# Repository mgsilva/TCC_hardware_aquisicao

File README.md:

# TCC - Hardware Aquisição
Layout da PCB do sistema de aquisição utilizado no Trabalho de Conclusão de Curso do CEFET-MG.

Tema: Projeto e implementação de uma plataforma IoT para monitoramento de motores de indução trifásicos.

Este hardware conta com um sensor de corrente, um filtro antialiasing, um conversor de nível e um ESP32.
O sistema é capaz de aquisitar sinais até 5Khz.

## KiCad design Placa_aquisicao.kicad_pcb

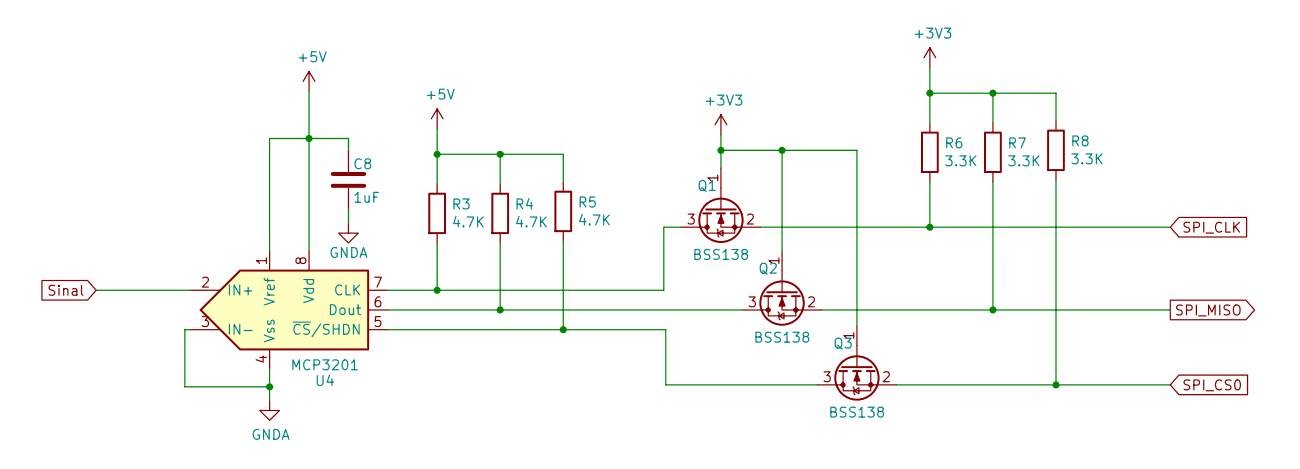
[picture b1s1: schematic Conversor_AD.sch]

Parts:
C8: 1uF; C_0805_2012Metric_Pad1.18x1.45mm_HandSolder
Q1, Q2, Q3: BSS138; SOT-23
R3, R4, R5: 4.7K; R_0805_2012Metric_Pad1.20x1.40mm_HandSolder
R6, R7, R8: 3.3K; R_0805_2012Metric_Pad1.20x1.40mm_HandSolder
U4: MCP3201; SOIC-8_3.9x4.9mm_P1.27mm

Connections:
+3V3: Q1.1 (G), Q2.1 (G), Q3.1 (G), R6.1, R7.1, R8.1; also elsewhere on the board
+5V: C8.1, R3.1, R4.1, R5.1, U4.1 (Vref), U4.8 (Vdd); also elsewhere on the board
GND: C8.2, U4.3 (IN-), U4.4 (Vss); also elsewhere on the board
unnamed: Q1.3 (D), R3.2, U4.7 (CLK)
unnamed: Q2.3 (D), R4.2, U4.6 (Dout)
unnamed: Q3.3 (D), R5.2, U4.5 (~CS~/SHDN)
SPI_CLK: Q1.2 (S), R6.2; also elsewhere on the board
SPI_CS0: Q3.2 (S), R8.2; also elsewhere on the board
SPI_MISO: Q2.2 (S), R7.2; also elsewhere on the board
Sinal: U4.2 (IN+); also elsewhere on the board

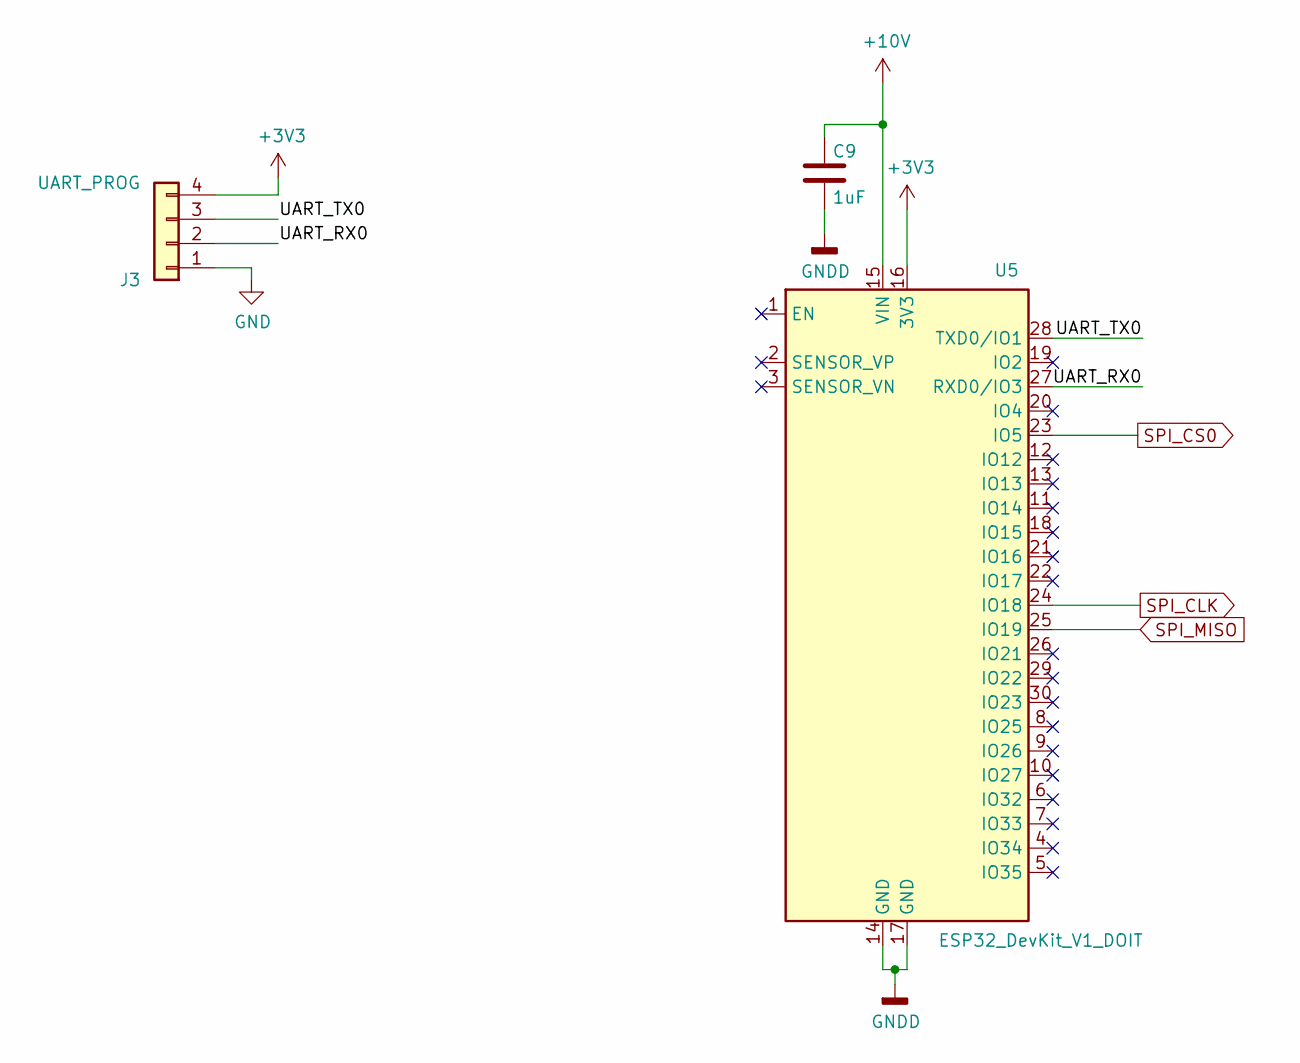
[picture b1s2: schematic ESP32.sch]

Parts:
C9: 1uF; C_0805_2012Metric_Pad1.18x1.45mm_HandSolder
J3: UART_PROG; Molex_KK-254_AE-6410-04A_1x04_P2.54mm_Vertical
U5: ESP32_DevKit_V1_DOIT; esp32_devkit_v1_doit

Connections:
+3V3: J3.4, U5.16 (3V3); also elsewhere on the board
+10V: C9.1, U5.15 (VIN); also elsewhere on the board
/ESP32/UART_RX0: J3.2, U5.27 (RXD0/IO3)
/ESP32/UART_TX0: J3.3, U5.28 (TXD0/IO1)
GND: C9.2, J3.1, U5.14 (GND), U5.17 (GND); also elsewhere on the board
SPI_CLK: U5.24 (IO18); also elsewhere on the board
SPI_CS0: U5.23 (IO5); also elsewhere on the board
SPI_MISO: U5.25 (IO19); also elsewhere on the board

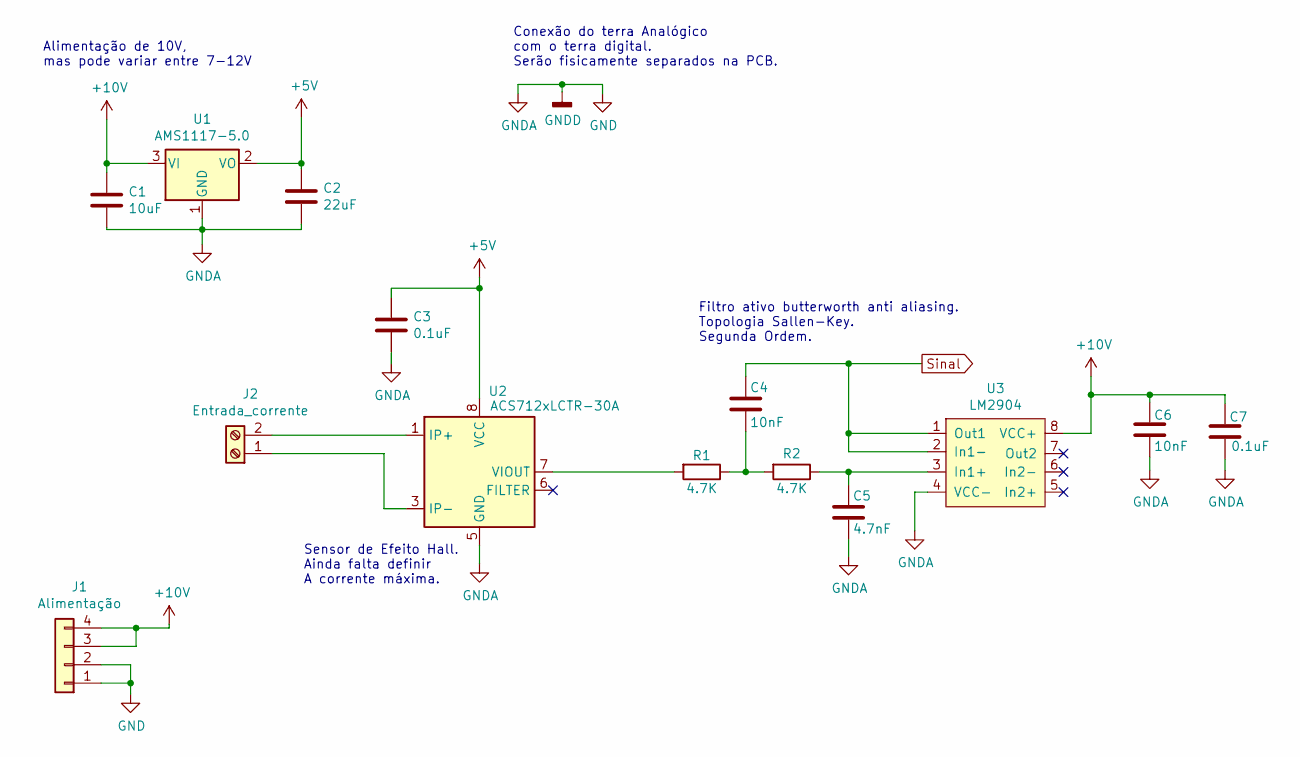
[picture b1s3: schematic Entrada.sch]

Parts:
C1: 10uF; C_0805_2012Metric_Pad1.18x1.45mm_HandSolder
C2: 22uF; C_1206_3216Metric_Pad1.33x1.80mm_HandSolder
C3, C7: 0.1uF; C_0805_2012Metric_Pad1.18x1.45mm_HandSolder
C4, C6: 10nF; C_0805_2012Metric_Pad1.18x1.45mm_HandSolder
C5: 4.7nF; C_0805_2012Metric_Pad1.18x1.45mm_HandSolder
J1: Alimentação; Molex_KK-254_AE-6410-04A_1x04_P2.54mm_Vertical
J2: Entrada_corrente; TerminalBlock_Phoenix_MKDS-1,5-2_1x02_P5.00mm_Horizontal
R1, R2: 4.7K; R_0805_2012Metric_Pad1.20x1.40mm_HandSolder
U1: AMS1117-5.0; SOT-223-3_TabPin2
U2: ACS712xLCTR-30A; SOIC-8_3.9x4.9mm_P1.27mm
U3: LM2904; SO-8_3.9x4.9mm_P1.27mm

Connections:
+5V: C2.1, C3.1, U1.2 (VO), U2.8 (VCC); also elsewhere on the board
+10V: C1.1, C6.1, C7.1, J1.3, J1.4, U1.3 (VI), U3.8 (VCC+); also elsewhere on the board
GND: C1.2, C2.2, C3.2, C5.2, C6.2, C7.2, J1.1, J1.2, U1.1 (GND), U2.5 (GND), U3.4 (VCC-); also elsewhere on the board
unnamed: C4.2, R1.1, R2.2
unnamed: C5.1, R2.1, U3.3 (In1+)
unnamed: J2.1, U2.3 (IP-), U2.4 (IP-)
unnamed: J2.2, U2.1 (IP+), U2.2 (IP+)
unnamed: R1.2, U2.7 (VIOUT)
Sinal: C4.1, U3.1 (Out1), U3.2 (In1-); also elsewhere on the board

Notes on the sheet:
Conexão do terra Analógico com o terra digital. Serão fisicamente separados na PCB.
Filtro ativo butterworth anti aliasing. Topologia Sallen-Key. Segunda Ordem.
Alimentação de 10V, mas pode variar entre 7-12V
Sensor de Efeito Hall. Ainda falta definir A corrente máxima.

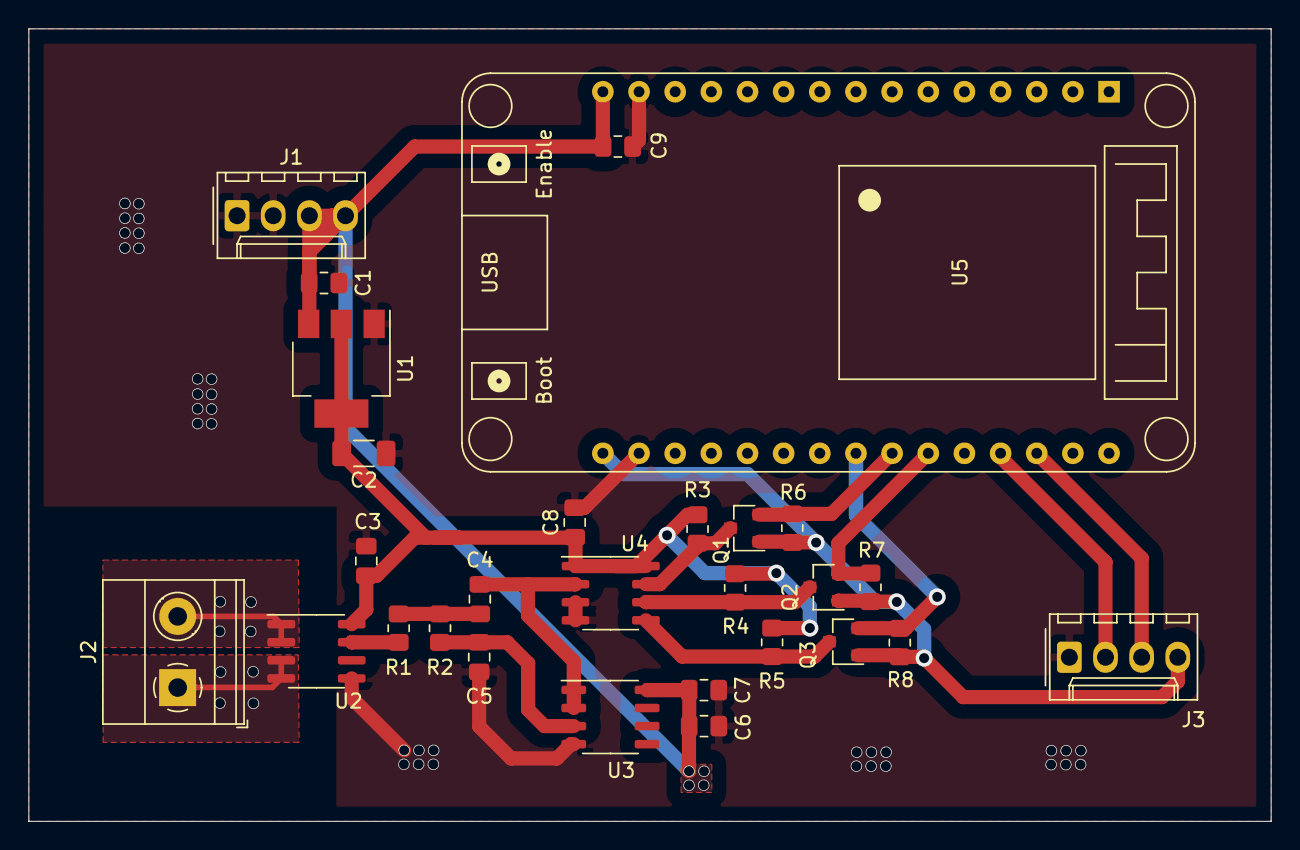
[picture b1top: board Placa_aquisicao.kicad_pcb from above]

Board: 2 copper layers, 87.3 x 55.7 mm, 28 parts (0 on the bottom side), 18 nets.

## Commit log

2021-08-11 Projeto finalizado
